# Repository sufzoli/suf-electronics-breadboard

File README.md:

suf-electronics-breadboard
==========================

No electronics breadboard accessories

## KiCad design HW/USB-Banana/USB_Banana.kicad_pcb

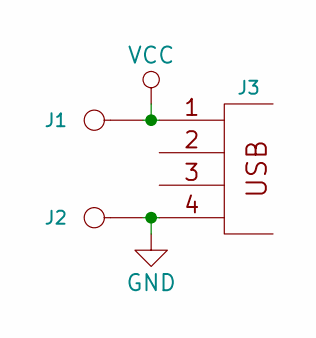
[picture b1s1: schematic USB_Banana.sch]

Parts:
J1, J2: CONN_1; BANANA-PLUG
J3: USB_2; USB-A_SMD

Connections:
GND: J2.1, J3.4
VCC: J1.1, J3.1

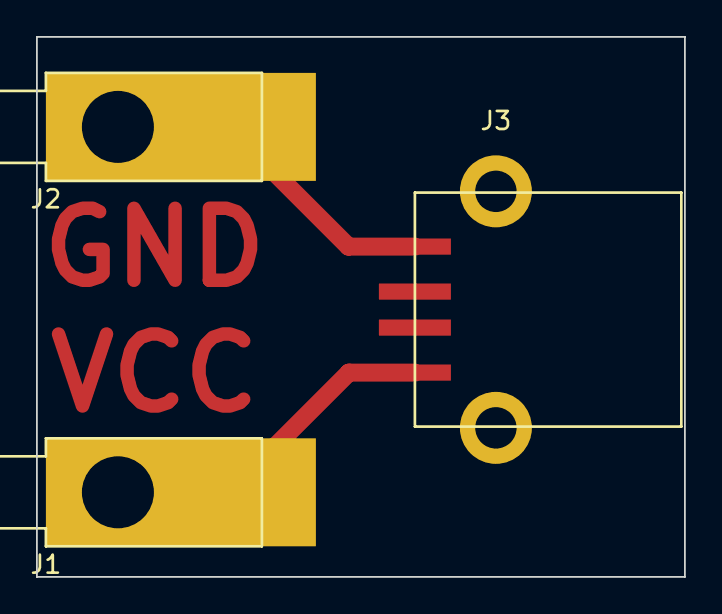
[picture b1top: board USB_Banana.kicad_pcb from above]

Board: 2 copper layers, 36.0 x 30.0 mm, 3 parts (0 on the bottom side), 2 nets.

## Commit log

2014-09-16 3.5 Jack and USB-B breakout added
2014-09-17 RCA added
2014-10-11 Minor cosmetic corrections
2021-03-20 Add S0-8 and USB_Banana
